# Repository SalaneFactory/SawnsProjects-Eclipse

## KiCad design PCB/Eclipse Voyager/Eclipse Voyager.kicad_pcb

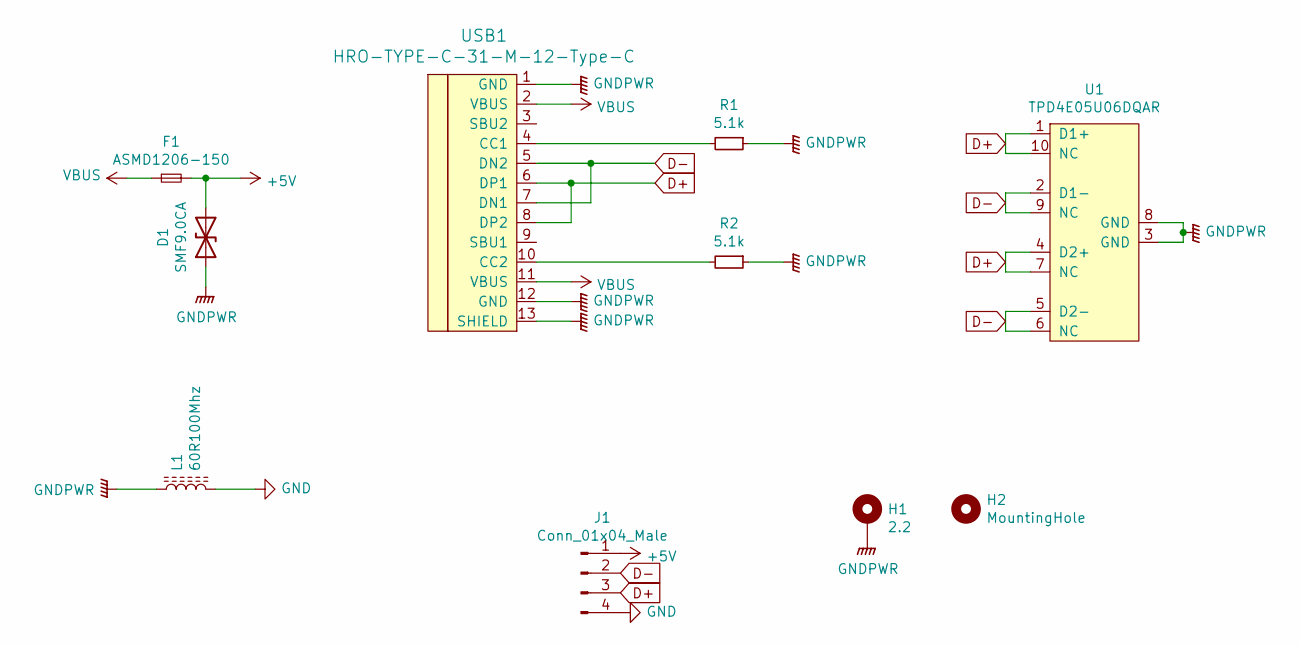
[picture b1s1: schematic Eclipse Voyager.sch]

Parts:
D1: SMF9.0CA; D_SOD-123_Bidirectional
F1: ASMD1206-150; Fuse_1206_3216Metric
H1: 2.2; MountingHole_2.2mm_M2_ISO7380_Pad
H2: MountingHole; MountingHole_2.2mm_M2_ISO7380_Pad_TopOnly
J1: Conn_01x04_Male; JST-SR-4
L1: 60R100Mhz; L_1206_3216Metric
R1, R2: 5.1k; R_0603
U1: TPD4E05U06DQAR; USON-10_2.5x1.0mm_P0.5mm
USB1: HRO-TYPE-C-31-M-12-Type-C; HRO-TYPE-C-31-M-12-Assembly

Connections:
+5V: D1.2 (A2), F1.2, J1.1
D+: J1.3, U1.1 (D1+), U1.4 (D2+), U1.7 (NC), U1.10 (NC), USB1.6 (DP1), USB1.8 (DP2)
D-: J1.2, U1.2 (D1-), U1.5 (D2-), U1.6 (NC), U1.9 (NC), USB1.5 (DN2), USB1.7 (DN1)
GND: J1.4, L1.2
GNDPWR: D1.1 (A1), H1.1, L1.1, R1.1, R2.1, U1.3 (GND), U1.8 (GND), USB1.1 (GND), USB1.12 (GND), USB1.13 (SHIELD)
unnamed: R1.2, USB1.4 (CC1)
unnamed: R2.2, USB1.10 (CC2)
VBUS: F1.1, USB1.2 (VBUS), USB1.11 (VBUS)

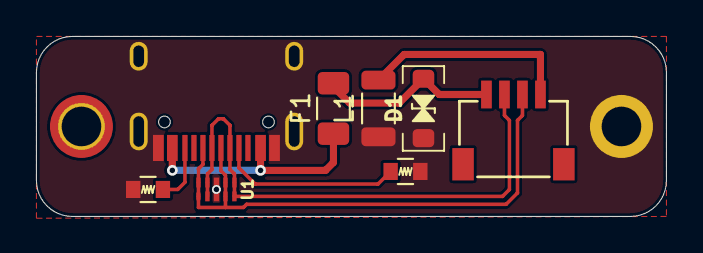
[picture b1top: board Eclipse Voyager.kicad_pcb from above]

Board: 2 copper layers, 35.0 x 10.0 mm, 10 parts (0 on the bottom side), 8 nets.

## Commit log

2022-10-08 PCB update
2022-10-08 Fix PCB error, Add keyswitch for 6U Spacebar PCB
